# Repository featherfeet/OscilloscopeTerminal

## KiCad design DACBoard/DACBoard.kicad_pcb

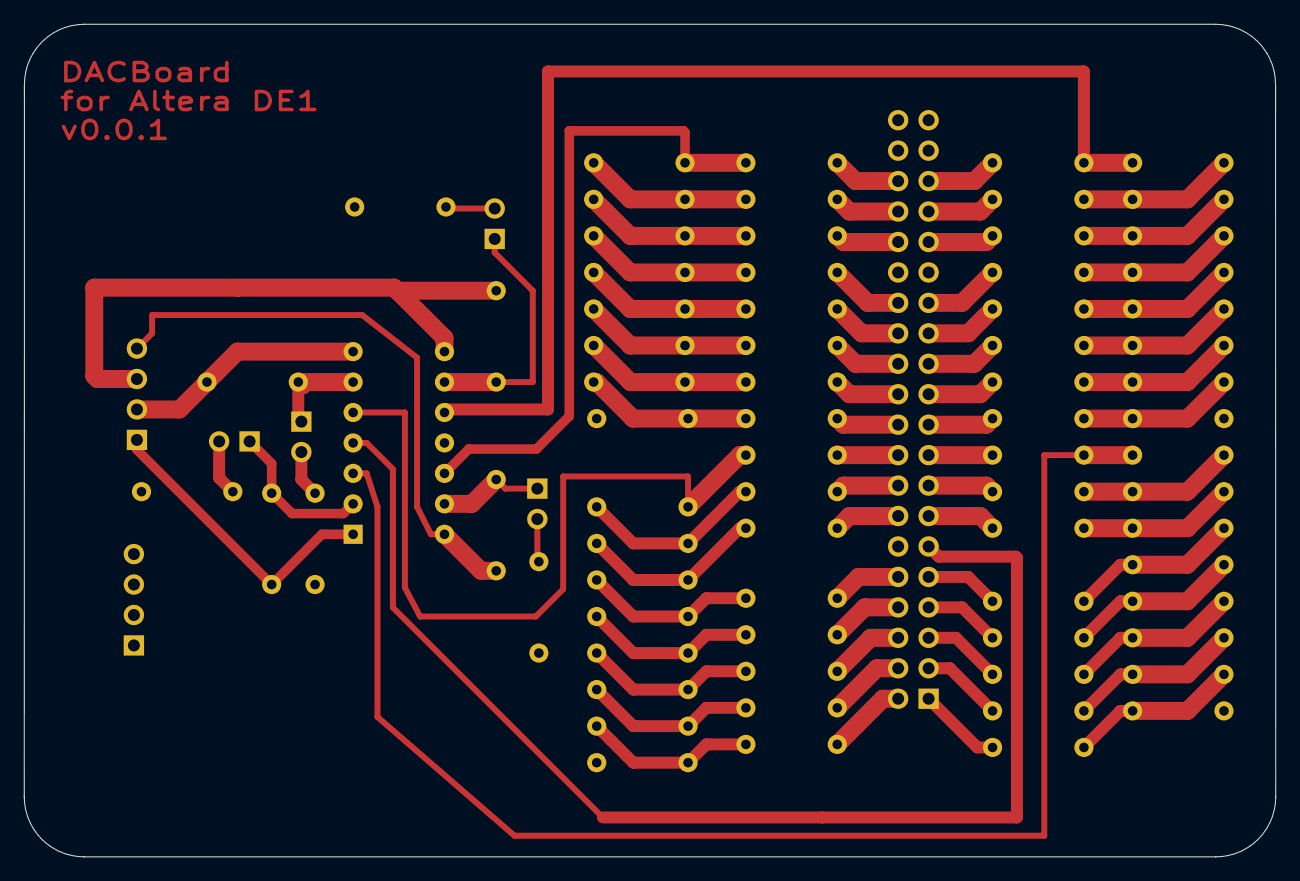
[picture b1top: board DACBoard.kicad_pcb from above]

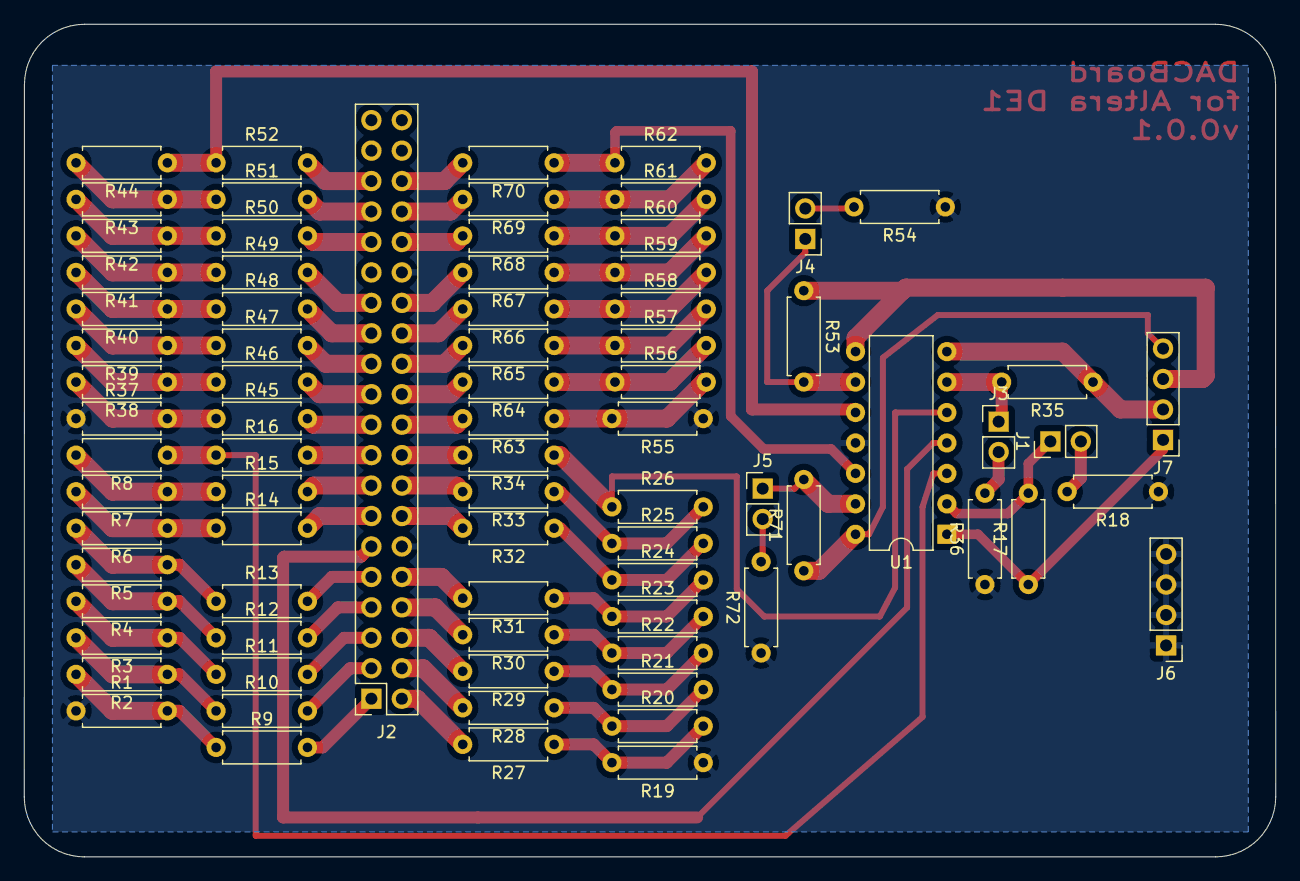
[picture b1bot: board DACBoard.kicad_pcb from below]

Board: 2 copper layers, 104.4 x 69.5 mm, 80 parts (80 on the bottom side), 78 nets.

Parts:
J1, J3, J4, J5: Conn_01x02_Male; PinHeader_1x02_P2.54mm_Vertical
J2: Conn_02x20_Odd_Even; PinSocket_2x20_P2.54mm_Vertical
J6, J7: Conn_01x04_Male; PinHeader_1x04_P2.54mm_Vertical
R1, R9, R10, R11, R12, R13, R14, R15, R16, R19, R27, R28, R29, R30, R31, R32, R33, R34, R37, R45, R46, R47, R48, R49, R50, R51, R52, R55, R63, R64, R65, R66, R67, R68, R69, R70: 200 K; R_Axial_DIN0207_L6.3mm_D2.5mm_P7.62mm_Horizontal
R2, R3, R4, R5, R6, R7, R8, R20, R21, R22, R23, R24, R25, R26, R38, R39, R40, R41, R42, R43, R44, R56, R57, R58, R59, R60, R61, R62: 100 K; R_Axial_DIN0207_L6.3mm_D2.5mm_P7.62mm_Horizontal
R17, R35, R53, R71: 1 K; R_Axial_DIN0207_L6.3mm_D2.5mm_P7.62mm_Horizontal
R18, R36, R54, R72: 2 K; R_Axial_DIN0207_L6.3mm_D2.5mm_P7.62mm_Horizontal
U1: MCP6004; DIP-14_W7.62mm

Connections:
/+5V: J2.11, U1.4
/IO_A0: J2.1, R9.2
/IO_A1: J2.2, R27.2
/IO_A2: J2.3, R10.2
/IO_A3: J2.4, R28.2
/IO_A4: J2.5, R11.2
/IO_A5: J2.6, R29.2
/IO_A6: J2.7, R12.2
/IO_A7: J2.8, R30.2
/IO_A8: J2.9, R13.2
/IO_A9: J2.10, R31.2
/IO_A10: J2.13, R14.2
/IO_A11: J2.14, R32.2
/IO_A12: J2.15, R15.2
/IO_A13: J2.16, R33.2
/IO_A14: J2.17, R16.2
/IO_A15: J2.18, R34.2
/IO_A16: J2.19, R45.2
/IO_A17: J2.20, R63.2
/IO_A18: J2.21, R46.2
/IO_A19: J2.22, R64.2
/IO_A20: J2.23, R47.2
/IO_A21: J2.24, R65.2
/IO_A22: J2.25, R48.2
/IO_A23: J2.26, R66.2
/IO_A24: J2.27, R49.2
/IO_A25: J2.28, R67.2
/IO_A26: J2.31, R50.2
/IO_A27: J2.32, R68.2
/IO_A28: J2.33, R51.2
/IO_A29: J2.34, R69.2
/IO_A30: J2.35, R52.2
/IO_A31: J2.36, R70.2
GND: J2.12, J2.30, J6.1, J6.2, J6.3, J6.4, R1.1, R18.1, R19.1, R36.1, R37.1, R54.1, R55.1, R72.1, U1.11
unnamed: J1.1, R17.2, U1.2
unnamed: J1.2, R18.2
unnamed: J3.1, R35.2, U1.6
unnamed: J3.2, R36.2
unnamed: J4.1, R53.2, U1.9
unnamed: J4.2, R54.2
unnamed: J5.1, R71.2, U1.13
unnamed: J5.2, R72.2
unnamed: J7.1, R17.1, U1.1
unnamed: J7.2, R35.1, U1.7
unnamed: J7.3, R53.1, U1.8
unnamed: J7.4, R71.1, U1.14
unnamed: R1.2, R2.2, R9.1
unnamed: R2.1, R3.2, R10.1
unnamed: R3.1, R4.2, R11.1
unnamed: R4.1, R5.2, R12.1
unnamed: R5.1, R6.2, R13.1
unnamed: R6.1, R7.2, R14.1
unnamed: R7.1, R8.2, R15.1
unnamed: R8.1, R16.1, U1.3
unnamed: R19.2, R20.2, R27.1
unnamed: R20.1, R21.2, R28.1
unnamed: R21.1, R22.2, R29.1
unnamed: R22.1, R23.2, R30.1
unnamed: R23.1, R24.2, R31.1
unnamed: R24.1, R25.2, R32.1
unnamed: R25.1, R26.2, R33.1
unnamed: R26.1, R34.1, U1.5
unnamed: R37.2, R38.2, R45.1
unnamed: R38.1, R39.2, R46.1
unnamed: R39.1, R40.2, R47.1
unnamed: R40.1, R41.2, R48.1
unnamed: R41.1, R42.2, R49.1
unnamed: R42.1, R43.2, R50.1
unnamed: R43.1, R44.2, R51.1
unnamed: R44.1, R52.1, U1.10
unnamed: R55.2, R56.2, R63.1
unnamed: R56.1, R57.2, R64.1
unnamed: R57.1, R58.2, R65.1
unnamed: R58.1, R59.2, R66.1
unnamed: R59.1, R60.2, R67.1
unnamed: R60.1, R61.2, R68.1
unnamed: R61.1, R62.2, R69.1
unnamed: R62.1, R70.1, U1.12

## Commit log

2021-11-11 Successfully drawing a Lissajous figure on an oscilloscope.
2021-11-24 Working on DAC PCB, about to make big design changes to it because the layout is impossible.
2021-11-25 Finished first version of design.
2021-12-14 v0.0.1 of the PCB -- manufactured on the Othermill in MIT Cypress EDS with these designs.
